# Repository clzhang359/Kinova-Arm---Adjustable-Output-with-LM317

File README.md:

# PCB for Adjusting the Voltage Output from the Kinova Arm End Effector with an LM317
_This repo was made by Connie L. Zhang at Georgia Tech at the SAFE Robotics Lab as a part of the Farmhand Project._

_Last Updated: 2025/05/02_

The 24V output of the Kinova Arm was too much for the microscope's motor (12V/1.5A), so the LM317 was applied to decrease the output voltage.

This PCB Design was made in KiCAD, and all design files can be found in the "kinova_arm_pcb_adjust" branch. The "fabexport_pwrpcb.zip" contains all the PCB manufacturing files.

This PCB goes on the Kinova Arm's End Effector and matches the provided pinout as shown below from the manual: 

## Why the LM317?

This specific device was chosen since (a) it was available at the HIVE makerspace, (b) I have used this in a previous class, and (c) the project fit the application.

The [LM317](https://www.st.com/resource/en/datasheet/lm217.pdf) is an adjustable voltage regulator that can input up to 40V and output anywhere between the provided input and 1.25V and up to 1.5A.

This schematic was taken from the datasheet has protection diodes to prevent any input short circuit and capacitance short circuit during capacitance discharge.

## Should I use this PCB for my project with my Kinova Arm?

Firstly, how much voltage and current does your voltage require?
- If it requries **less than 24V & less than 1.5A**, then yes, you can use this PCB.
- If it requries **less than 1.25V**, then **do not** use this PCB design.
- If it requires **more than 1.5A**, then **do not** use this PCB design.
- If it requires **more than 24V & less than 1.5A**, then **do not** use the LM317 or this PCB.

## Parts List:
- 1 x LM317
- 1 x 0.1uF capacitor
- 1 x 10uF capacitor
- 1 x 1uF capacitor
- 2 x 1N4001 diodes
- 1 x 1kΩ resistor
- 1 x 3-prong 10kΩ variable resistor

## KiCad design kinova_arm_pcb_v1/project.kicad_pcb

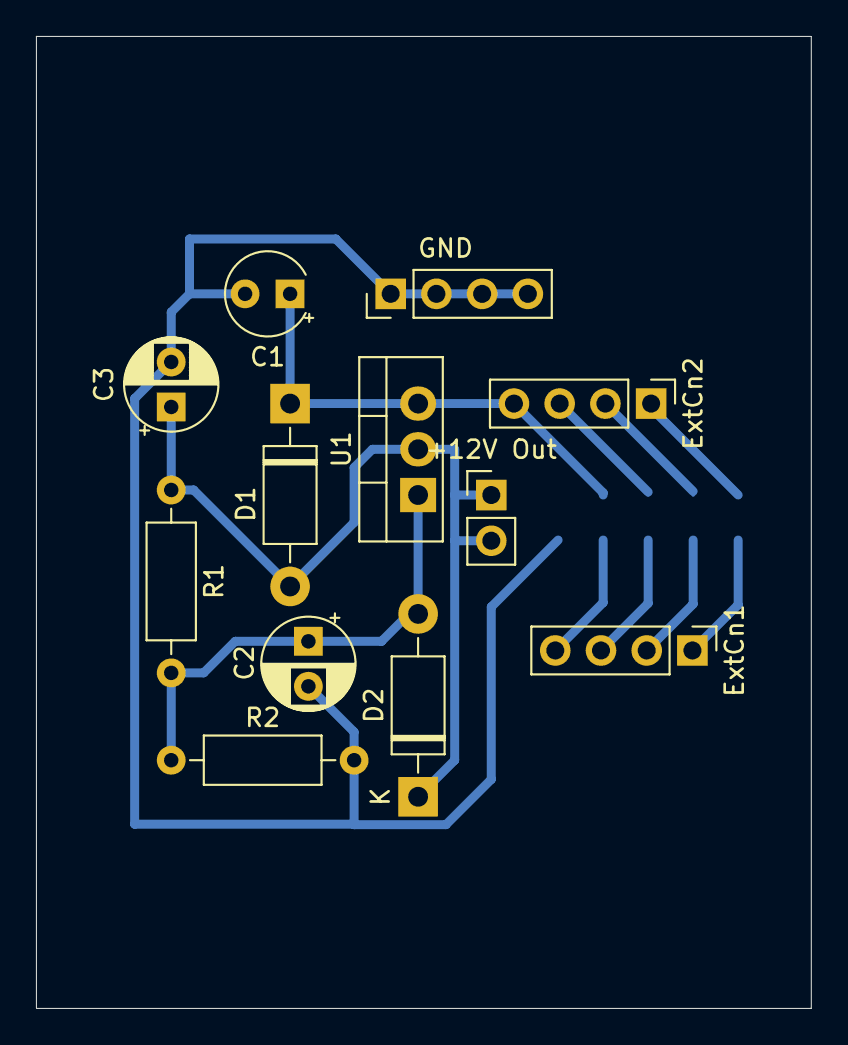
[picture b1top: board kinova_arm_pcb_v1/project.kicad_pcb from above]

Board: 2 copper layers, 43.0 x 54.0 mm, 13 parts (1 on the bottom side), 10 nets.

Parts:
2x5: 2x5
+12V Out: PinHeader_1x02_P2.54mm_Vertical
C1: 0.1u; CP_Radial_Tantal_D4.5mm_P2.50mm
C2: 10u; CP_Radial_D5.0mm_P2.50mm
C3: 1u; CP_Radial_D5.0mm_P2.50mm
D1, D2: 1N4001; D_DO-41_SOD81_P10.16mm_Horizontal
ExtCn1, ExtCn2: PinHeader_1x04_P2.54mm_Vertical
GND: PinHeader_1x04_P2.54mm_Vertical
R1: 1000; R_Axial_DIN0207_L6.3mm_D2.5mm_P10.16mm_Horizontal
R2: 8600; R_Axial_DIN0207_L6.3mm_D2.5mm_P10.16mm_Horizontal
U1: LM317_TO-220; TO-220-3_Vertical

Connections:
485 GND: 2x5.2, ExtCn1.1
485+: 2x5.3, ExtCn2.2
485-: 2x5.4, ExtCn1.2
+24V: 2x5.7, 2x5.8, C1.1, D1.1 (K), ExtCn1.4, ExtCn2.4, U1.3 (VI)
/Vout = +12V: +12V Out.1, +12V Out.2, C3.1, D1.2 (A), D2.1 (K), R1.1, U1.2 (VO)
Earth: 2x5.5, ExtCn2.3
GND: 2x5.9, 2x5.10, C1.2, C2.2, C3.2, GND.1, GND.2, GND.3, GND.4, R2.2
Intern: 2x5.1, ExtCn2.1
unnamed: C2.1, D2.2 (A), R1.2, R2.1, U1.1 (ADJ)
Von: 2x5.6, ExtCn1.3

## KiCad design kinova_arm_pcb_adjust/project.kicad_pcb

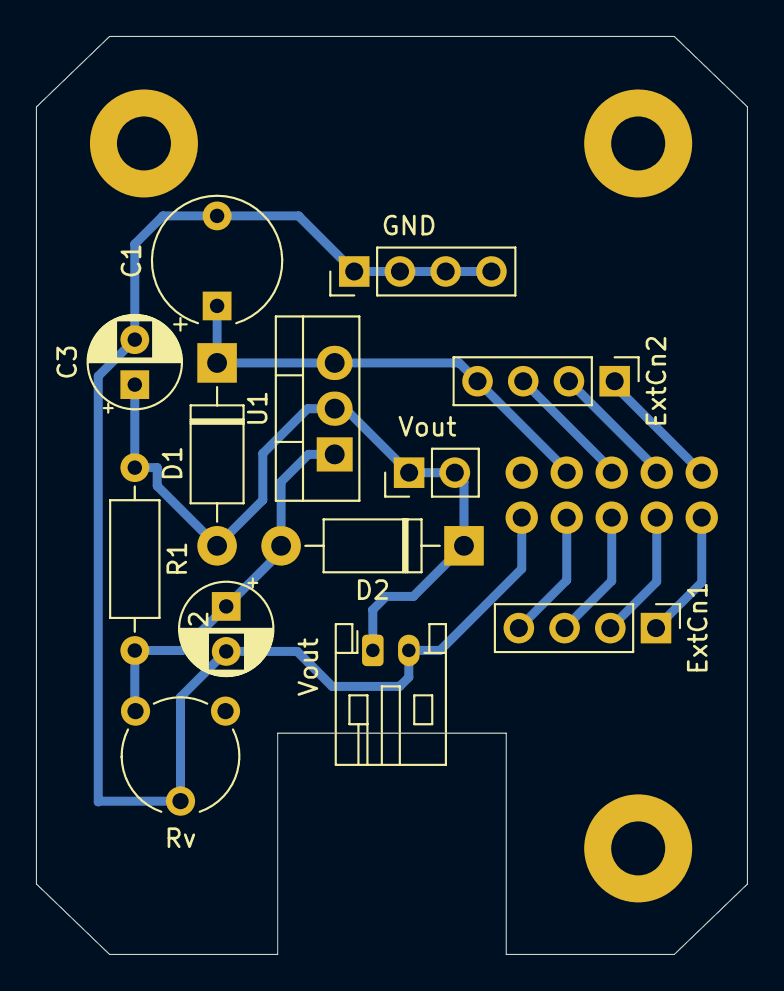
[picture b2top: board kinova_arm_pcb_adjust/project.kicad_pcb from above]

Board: 2 copper layers, 39.5 x 51.0 mm, 14 parts (1 on the bottom side), 10 nets.

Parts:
2x5_thr: 2x5_thr
C1: 0.1u; CP_Radial_Tantal_D7.0mm_P5.00mm
C2: 10u; CP_Radial_D5.0mm_P2.50mm
C3: 1u; CP_Radial_D5.0mm_P2.50mm
D1, D2: 1N4001; D_DO-41_SOD81_P10.16mm_Horizontal
ExtCn1, ExtCn2: PinHeader_1x04_P2.54mm_Vertical
GND: PinHeader_1x04_P2.54mm_Vertical
R1: 1000; R_Axial_DIN0207_L6.3mm_D2.5mm_P10.16mm_Horizontal
Rv: ClkWs-/CClkWs+; Potentiometer_Piher_PT-6-V_Vertical
U1: LM317_TO-220; TO-220-3_Vertical
Vout: JST_PH_S2B-PH-K_1x02_P2.00mm_Horizontal
Vout#2: PinHeader_1x02_P2.54mm_Vertical

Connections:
485 GND: 2x5_thr.6, ExtCn1.1
485+: 2x5_thr.2, ExtCn2.2
485-: 2x5_thr.7, ExtCn1.2
+24V: 2x5_thr.4, 2x5_thr.9, C1.1, D1.1 (K), ExtCn1.4, ExtCn2.4, U1.3 (VI)
/Vout = +12V: C3.1, D1.2 (A), D2.1 (K), R1.1, U1.2 (VO), Vout.1, Vout#2.2
Earth: 2x5_thr.3, ExtCn2.3
GND: 2x5_thr.5, 2x5_thr.10, C1.2, C2.2, C3.2, GND.1, GND.2, GND.3, GND.4, Rv.2, Vout.2
Intern: 2x5_thr.1, ExtCn2.1
unnamed: C2.1, D2.2 (A), R1.2, Rv.1, U1.1 (ADJ)
Von: 2x5_thr.8, ExtCn1.3

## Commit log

2025-05-02 Create kinova_arm_pcb_adjust
2025-05-02 Rename LM317.pdf to LM317_Datasheet.pdf
2025-05-02 Create f
2025-05-02 Create kinova_arm_pcb_projectv1
2025-05-02 Create images
2025-05-02 Rename image.png to kinova_pinout.png
2025-05-02 Rename Screenshot 2025-05-02 043846.png to schematic
2025-05-02 Rename schematic to schematic.png
2025-05-02 Rename Screenshot 2025-05-02 045001.png to 3D_pcb_view
